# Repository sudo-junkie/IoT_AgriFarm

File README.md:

# IoT_AgriFarm

KiCad 7 design files (schematic, PCB, BOM, gerbers) for a solar powered smart farm controller based on RP2040

-	USB-C - firmware upload & debugging
-	24V 2A Boost converter - to power water pump
-	RS-485 transciever - for NPK sensor
-	Soil moisture, soil temperature, soil PH relative humidity and ambient temperature sensors

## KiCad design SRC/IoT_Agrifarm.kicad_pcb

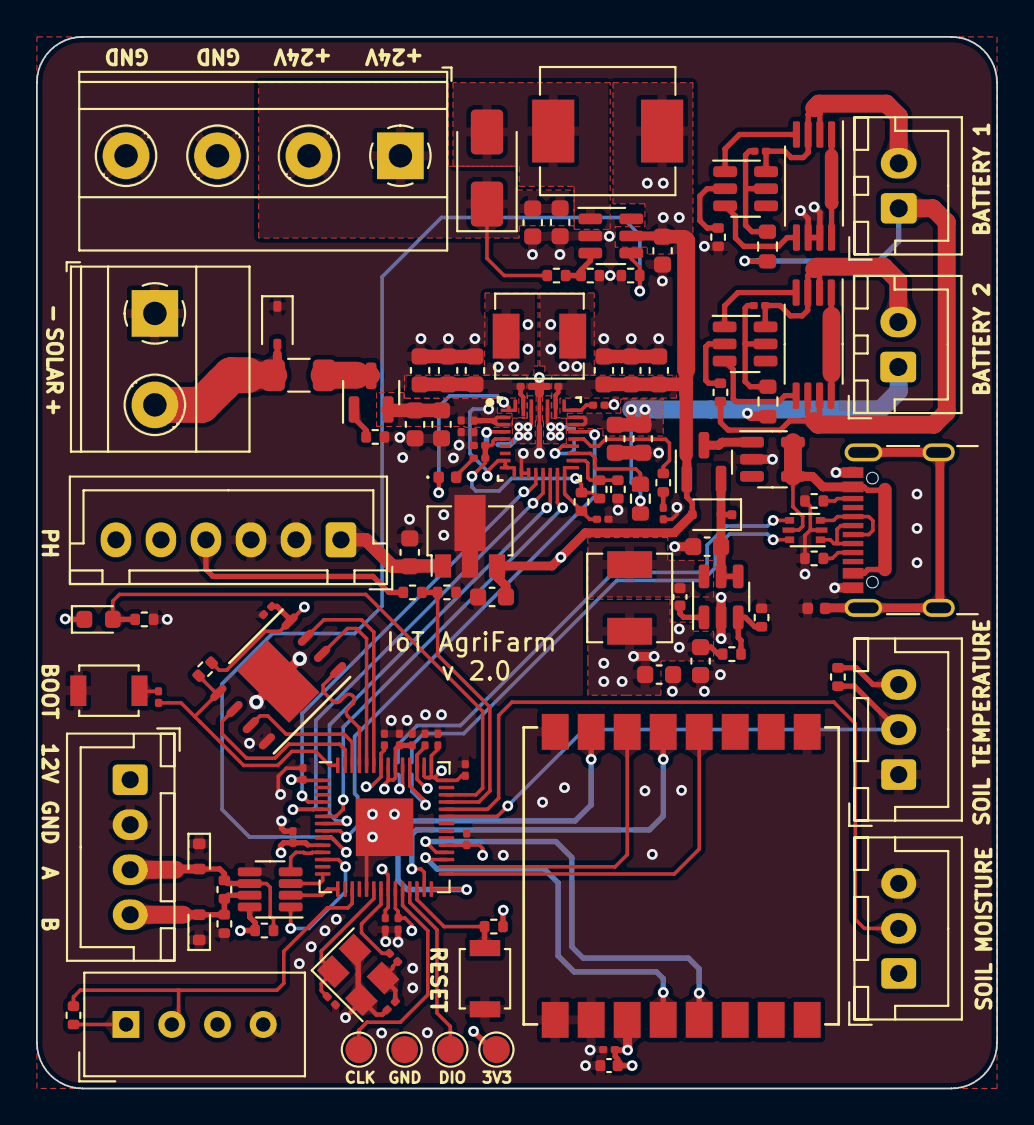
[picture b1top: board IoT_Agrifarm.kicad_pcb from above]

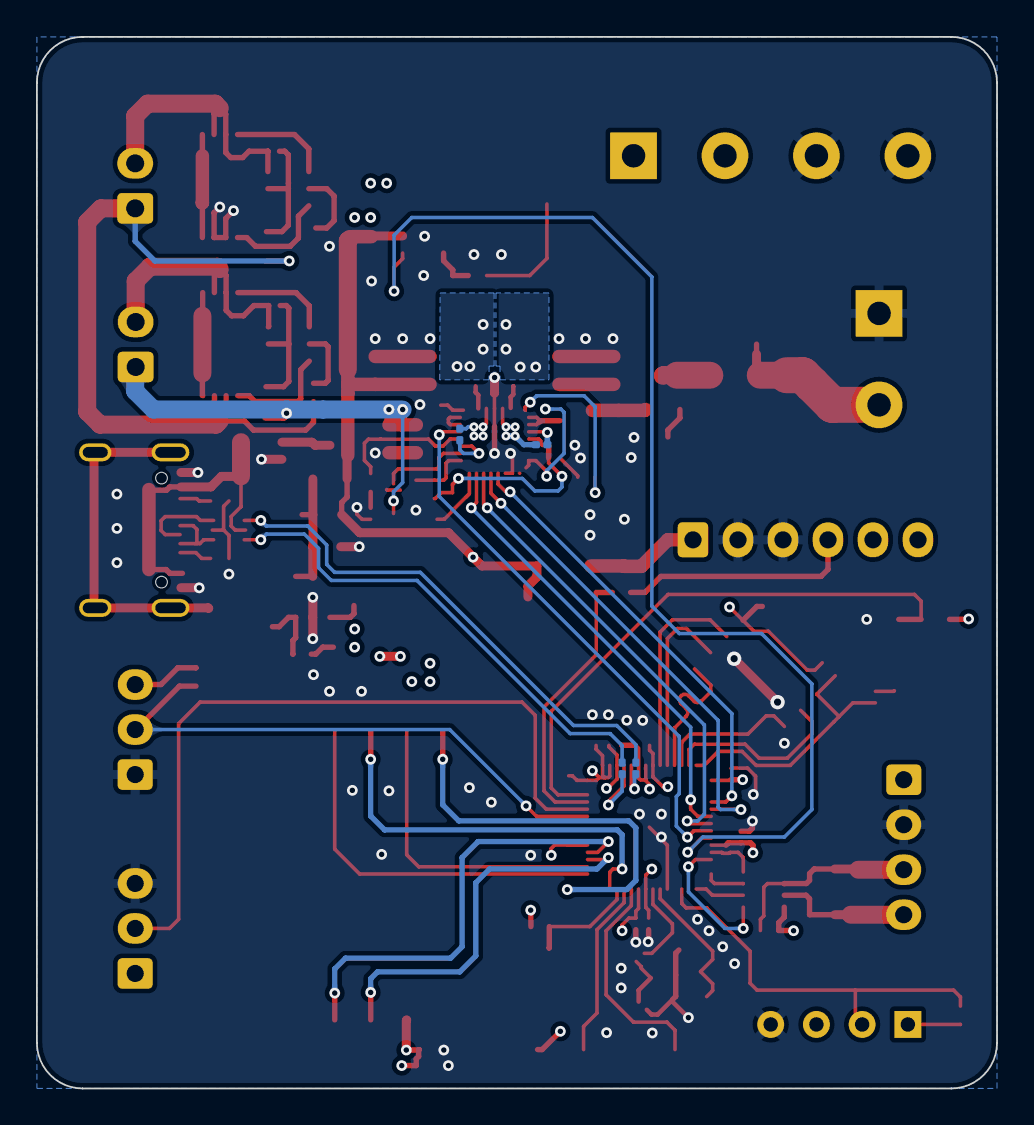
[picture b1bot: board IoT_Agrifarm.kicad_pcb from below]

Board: 4 copper layers, 53.3 x 58.4 mm, 124 parts (4 on the bottom side), 92 nets.

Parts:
BT201: BATT2; JST_XH_B2B-XH-A_1x02_P2.50mm_Vertical
BT202: BATT1; JST_XH_B2B-XH-A_1x02_P2.50mm_Vertical
C201, C202, C205, C207, C209, C214, C218, C301, C302, C303, C304, C305, C306, C307, C311, C312, C314, C502: 100n; C_0201_0603Metric
C203, C204, C210, C211, C212, C215, C216, C217, C219, C220, C221, C222, C224, C225, C226, C601, C602, C603: 10u; C_0603_1608Metric
C206: 1n; C_0201_0603Metric
C208, C213: 47n; C_0201_0603Metric
C223: 22n; C_0402_1005Metric
C308, C313: 1u; C_0201_0603Metric
C309, C310: 22p; C_0201_0603Metric
C501: 2u2; C_0402_1005Metric
D101: D_TVS; D_SOD-323
D201: LED_STAT; LED_0402_1005Metric
D202: 2.5A; D_SOD-323F
D401, D402: ESD131; D_SOD-523
D601: SS34; D_SMA
F101: Fuse; Fuse_1206_3216Metric
J101: J_PUMP; TerminalBlock_Phoenix_MKDS-1,5-4-5.08_1x04_P5.08mm_Horizont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
J102: J_PANEL; TerminalBlock_Phoenix_MKDS-1,5-2-5.08_1x02_P5.08mm_Horizont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
J103: Conn_NPK; JST_XH_B4B-XH-A_1x04_P2.50mm_Vertical
J104: USB_C_Receptacle_USB2.0; USB_C_Receptacle_GCT_USB4105-xx-A_16P_TopMnt_Horizontal
J401: Conn_PH; JST_XH_B6B-XH-A_1x06_P2.50mm_Vertical
J402: Conn_MOISTURE; JST_XH_B3B-XH-A_1x03_P2.50mm_Vertical
L101: 1u 10% 15mA; L_0402_1005Metric
L201, L202: 1u 20% 4.5A; L_Sunlord_MWSA0412S
L601: 10u; L_Sunlord_MWSA0603S
Q101, Q201: AO3401A; SOT-23
Q401: Q_Photo_NPN; LED_0603_1608Metric
R101, R305, R404, R405, R406, R407, R408: 10K; R_0402_1005Metric
R102, R103, R208, R211, R603: 5K1; R_0402_1005Metric
R201, R205, R207: 100R; R_0603_1608Metric
R202, R210, R304, R401, R402, R403: 1K; R_0402_1005Metric
R203: 127K; R_0402_1005Metric
R204, R213: 100K; R_0402_1005Metric
R206: 2K2; R_0201_0603Metric
R209: 33K; R_0201_0603Metric
R212, R301, R306: 1.05K; R_0201_0603Metric
R214: 25K5; R_0402_1005Metric
R302, R303: 27R; R_0201_0603Metric
R601: 200K; R_0402_1005Metric
R602: 1M; R_0402_1005Metric
SW301: SW_Push; SW_SPST_B3U-1000P
SW302: SW_BOOT; SW_SPST_B3U-1000P
TP301: TP_3V3; TestPoint_Pad_D1.5mm
TP302: TP_SWDCLK; TestPoint_Pad_D1.5mm
TP303: TP_GND; TestPoint_Pad_D1.5mm
TP304: TP_SWDIO; TestPoint_Pad_D1.5mm
U101: AP2171W; SOT-23-5
U102: USBLC6-2P6; SOT-666
U201, U204: DW01A; SOT-23-6
U202, U205: 8205A; TSSOP-8_4.4x3mm_P0.65mm
U203: BQ25672RQMR; RQM0029A-MFG
U206: L78L05; SOT-89-3
U207: SD8942; SOT-23-6
U301: RP2040; QFN-56-1EP_7x7mm_P0.4mm_EP3.2x3.2mm
U302: 25Q128; DFN-S-8-1EP_6x5mm_P1.27mm
U401: DS18B20; JST_XH_B3B-XH-A_1x03_P2.50mm_Vertical
U402: DHT11; Aosong_DHT11_5.5x12.0_P2.54mm
U403: MAX3362; SOT-23-8
U501: Ai-Thinker-Ra-02; Ai-Thinker-Ra-01-LoRa
U601: SY7208; SOT-23-6
Y301: 12MHz; Crystal_SMD_3225-4Pin_3.2x2.5mm

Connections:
+1V1: C311.1, C312.1, C313.1, U301.23 (DVDD), U301.45 (VREG_VOUT), U301.50 (DVDD)
+3V3: C225.1, C226.1, C301.1, C302.1, C303.1, C304.1, C305.1, C306.1, C307.1, C308.1, C314.1, C501.1, C502.1, J402.1, L202.1, Q401.1 (C), R213.2, R304.2, R305.2, R401.1, R402.1, R404.1, TP301.1, U301.1 (IOVDD), U301.10 (IOVDD), U301.22 (IOVDD), U301.33 (IOVDD), U301.42 (IOVDD), U301.43 (ADC_AVDD), U301.44 (VREG_IN), U301.48 (USB_VDD), U301.49 (IOVDD), U302.8 (VCC), U401.3 (V_{DD}), U402.1 (VCC), U403.8 (VCC), U501.3 (VDD)
+5V: C222.1, J401.1, U206.1 (OUT)
+12V: C214.1, C215.1, C216.1, C217.1, C221.1, C601.1, D202.2 (A), J103.1, L601.1, Q201.1 (G), U203.25 (SYS), U206.3 (IN), U601.5 (VIN)
/IOT_AGRIFARM_POWER/BATT1+: BT202.1 (+), R202.2, R207.1, U202.6 (S2), U202.7 (S2)
/IOT_AGRIFARM_POWER/BATT1-: BT202.2 (-), C218.2, U204.6 (GND), U205.2 (S1), U205.3 (S1)
/IOT_AGRIFARM_POWER/BATT2+: BT201.1 (+), C219.1, C220.1, R201.1, R205.2, U203.22 (BAT), U203.23 (BAT)
/IOT_AGRIFARM_POWER/BATT2-: BT201.2 (-), C205.2, U201.6 (GND), U202.2 (S1), U202.3 (S1)
/IOT_AGRIFARM_POWER/BQ_SCL: U203.14 (SCL), U301.7 (GPIO5)
/IOT_AGRIFARM_POWER/BQ_SDA: U203.15 (SDA), U301.6 (GPIO4)
/IOT_AGRIFARM_POWER/BQ_~CE: U203.13 (~CE), U301.5 (GPIO3)
/IOT_AGRIFARM_POWER/BQ_~INT: U203.21 (~INT), U301.8 (GPIO6)
/IOT_AGRIFARM_POWER/BQ_~QON: U203.12 (~QON), U301.4 (GPIO2)
/IOT_AGRIFARM_POWER/BUCK_IN: C224.1, D202.1 (K), Q201.2 (S), U207.4 (EN), U207.5 (VIN)
/IOT_AGRIFARM_POWER/BUCK_SW: C223.2, L202.2, U207.6 (SW)
/IOT_AGRIFARM_POWER/PMID: C209.1, C210.1, C211.1, C212.1, U203.29 (PMID)
/IOT_AGRIFARM_POWER/REGN: C207.1, R203.1, R206.1, R208.1, U203.5 (REGN)
/IOT_AGRIFARM_POWER/SW1: C208.1, L201.1, U203.28 (SW1)
/IOT_AGRIFARM_POWER/SW2: C213.1, L201.2, U203.26 (SW2)
/IOT_AGRIFARM_POWER/V_PANEL: C201.1, C202.1, C203.1, C204.1, Q101.2 (S), U203.2 (VBUS), U203.3 (VBUS), U203.8 (VAC2), U203.9 (VAC1)
/IOT_AGRIFARM_SENSORS/485_RX: U301.12 (GPIO9), U403.1 (RO)
/IOT_AGRIFARM_SENSORS/485_TX: U301.11 (GPIO8), U403.4 (DI)
/IOT_AGRIFARM_SENSORS/485_TX_EN: U301.14 (GPIO11), U403.3 (DE)
/IOT_AGRIFARM_SENSORS/DHT_SENSOR: R402.2, U301.17 (GPIO14), U402.2 (IO)
/IOT_AGRIFARM_SENSORS/LIGHT_SENSOR: Q401.2 (E), R403.1, U301.40 (GPIO28_ADC2)
/IOT_AGRIFARM_SENSORS/NPK_A: D402.2 (A2), J103.3, R404.2, R406.1, U403.6 (A)
/IOT_AGRIFARM_SENSORS/NPK_B: D401.2 (A2), J103.4, R406.2, R408.1, U403.7 (B)
/IOT_AGRIFARM_SENSORS/SOIL_MOISTURE: J402.2, U301.38 (GPIO26_ADC0)
/IOT_AGRIFARM_SENSORS/SOIL_PH: R405.2, R407.1, U301.39 (GPIO27_ADC1)
/IOT_AGRIFARM_SENSORS/SOIL_TEMP: R401.2, U301.37 (GPIO25), U401.2 (DQ)
/IOT_AGRIFARM_SENSORS/~485_RX_EN: U301.15 (GPIO12), U403.2 (~RE)
/MCU_RP2040/GPIO7: R602.2, U301.9 (GPIO7), U601.4 (EN)
/MCU_RP2040/GPIO16: U301.27 (GPIO16), U501.13 (MISO)
/MCU_RP2040/GPIO17: U301.28 (GPIO17), U501.15 (~NSS)
/MCU_RP2040/GPIO18: U301.29 (GPIO18), U501.12 (SCK)
/MCU_RP2040/GPIO19: U301.30 (GPIO19), U501.14 (MOSI)
/MCU_RP2040/GPIO20: U301.31 (GPIO20), U501.4 (~RESET)
/MCU_RP2040/GPIO21: U301.32 (GPIO21), U501.5 (DIO0)
/MCU_RP2040/QSPI_CLK: U301.52 (QSPI_SCLK), U302.6 (CLK)
/MCU_RP2040/QSPI_SD0: U301.53 (QSPI_SD0), U302.5 (DI(IO0))
/MCU_RP2040/QSPI_SD1: U301.55 (QSPI_SD1), U302.2 (DO(IO1))
/MCU_RP2040/QSPI_SD2: U301.54 (QSPI_SD2), U302.3 (IO2)
/MCU_RP2040/QSPI_SD3: U301.51 (QSPI_SD3), U302.7 (IO3)
/MCU_RP2040/QSPI_SS: R304.1, R306.1, U301.56 (QSPI_SS), U302.1 (~CS)
/MCU_RP2040/RESET: R305.1, SW301.2, U301.26 (RUN)
/MCU_RP2040/SWCLK: TP302.1, U301.24 (SWCLK)
/MCU_RP2040/SWDIO: TP304.1, U301.25 (SWD)
/MCU_RP2040/USB_DN: R303.1, U102.6 (I/O1)
/MCU_RP2040/USB_DP: R302.1, U102.4 (I/O2)
/MCU_RP2040/XIN: C309.1, U301.20 (XIN), Y301.1
/MCU_RP2040/XOUT: R301.2, U301.21 (XOUT)
/REGULATOR_SWITCHING_SY7208/SW_24V: D601.2 (A), L601.2, U601.1 (LX)
/REGULATOR_SWITCHING_SY7208/VOUT_24V: C602.1, C603.1, D601.1 (K), J101.1, J101.2, R601.2
/USB_DN: J104.A7 (D-), J104.B7 (D-), U102.1 (I/O1)
/USB_DP: J104.A6 (D+), J104.B6 (D+), U102.3 (I/O2)
/VBUS_IN: J104.A4 (VBUS), J104.A9 (VBUS), J104.B4 (VBUS), J104.B9 (VBUS), U101.4 (EN), U101.5 (IN), U102.5 (VBUS)
Earth: J104.S1 (SHIELD), L101.1
GND: C201.2, C202.2, C203.2, C204.2, C206.1, C207.2, C209.2, C210.2, C211.2, C212.2, C214.2, C215.2, C216.2, C217.2, C219.2, C220.2, C221.2, C222.2, C224.2, C225.2, C226.2, C301.2, C302.2, C303.2, C304.2, C305.2, C306.2, C307.2, C308.2, C309.2, C310.2, C311.2, C312.2, C313.2, C314.2, C501.2, C502.2, C601.2, C602.2, C603.2, D101.1 (A1), D401.1 (A1), D402.1 (A1), J101.3, J101.4, J102.1, J103.2, J104.A1 (GND), J104.A12 (GND), J104.B1 (GND), J104.B12 (GND), J401.2, J401.3, J402.3, L101.2, R101.1, R102.2, R103.2, R204.2, R209.2, R210.2, R212.2, R214.1, R403.2, R407.2, R408.2, R602.1, R603.1, SW301.1, SW302.1, TP303.1, U101.2 (GND), U102.2 (GND), U203.10 (ACDRV2), U203.11 (ACDRV1), U203.27 (GND), U205.6 (S2), U205.7 (S2), U206.2 (GND), U207.2 (GND), U301.19 (TESTEN), U301.57 (GND), U302.4 (GND), U302.9 (EP), U401.1 (GND), U402.4 (GND), U403.5 (GND), U501.1 (GND), U501.2 (GND), U501.9 (GND), U501.16 (GND), U601.2 (GND), Y301.2, Y301.4
unnamed: C310.1, R301.1, Y301.3
unnamed: D101.2 (A2), F101.1, J102.2
unnamed: D201.2 (A), R206.2
unnamed: D201.1 (K), U203.1 (STAT)
unnamed: J104.A5 (CC1), R102.1
unnamed: J104.B5 (CC2), R103.1
unnamed: J401.4, R405.1
unnamed: F101.2, Q101.3 (D)
unnamed: Q101.1 (G), R101.2
unnamed: R211.1, R212.1
unnamed: R306.2, SW302.2
unnamed: R202.1, U201.2 (CS)
unnamed: U201.3 (OC), U202.5 (G2)
unnamed: U201.1 (OD), U202.4 (G1)
unnamed: C205.1, R201.2, U201.5 (VCC)
unnamed: U202.1 (D1), U202.8 (D2)
unnamed: R205.1, U203.18 (BATP)
unnamed: C208.2, U203.4 (BTST1)
unnamed: C213.2, U203.19 (BTST2)
unnamed: R203.2, R204.1, U203.17 (ILIM_HIZ)
unnamed: R211.2, U203.20 (PROG)
unnamed: C206.2, U203.24 (SDRV)
unnamed: R208.2, R209.1, U203.16 (TS)
unnamed: R210.1, U204.2 (CS)
unnamed: U204.3 (OC), U205.5 (G2)
unnamed: U204.1 (OD), U205.4 (G1)
unnamed: C218.1, R207.2, U204.5 (VCC)
unnamed: U205.1 (D1), U205.8 (D2)
unnamed: C223.1, U207.1 (BS)
unnamed: R213.1, R214.2, U207.3 (FB)
unnamed: R303.2, U301.46 (USB_DM)
unnamed: R302.2, U301.47 (USB_DP)
unnamed: R601.1, R603.2, U601.3 (FB)
VBUS: Q201.3 (D), U101.1 (OUT)

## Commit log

2023-07-06 Version 2 - Added 24V 2A Boost converter for water pump
